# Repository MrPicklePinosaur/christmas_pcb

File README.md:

<div align="center">

# christmas pcb

</div>

Retrieving models from JLCPCB using the [JLC2KiCad](https://github.com/TousstNicolas/JLC2KiCad_lib) tool
```
JLC2KiCadLib C70378 -dir lib -model_dir models -footprint_lib footprints -symbol_lib_dir symbols
```

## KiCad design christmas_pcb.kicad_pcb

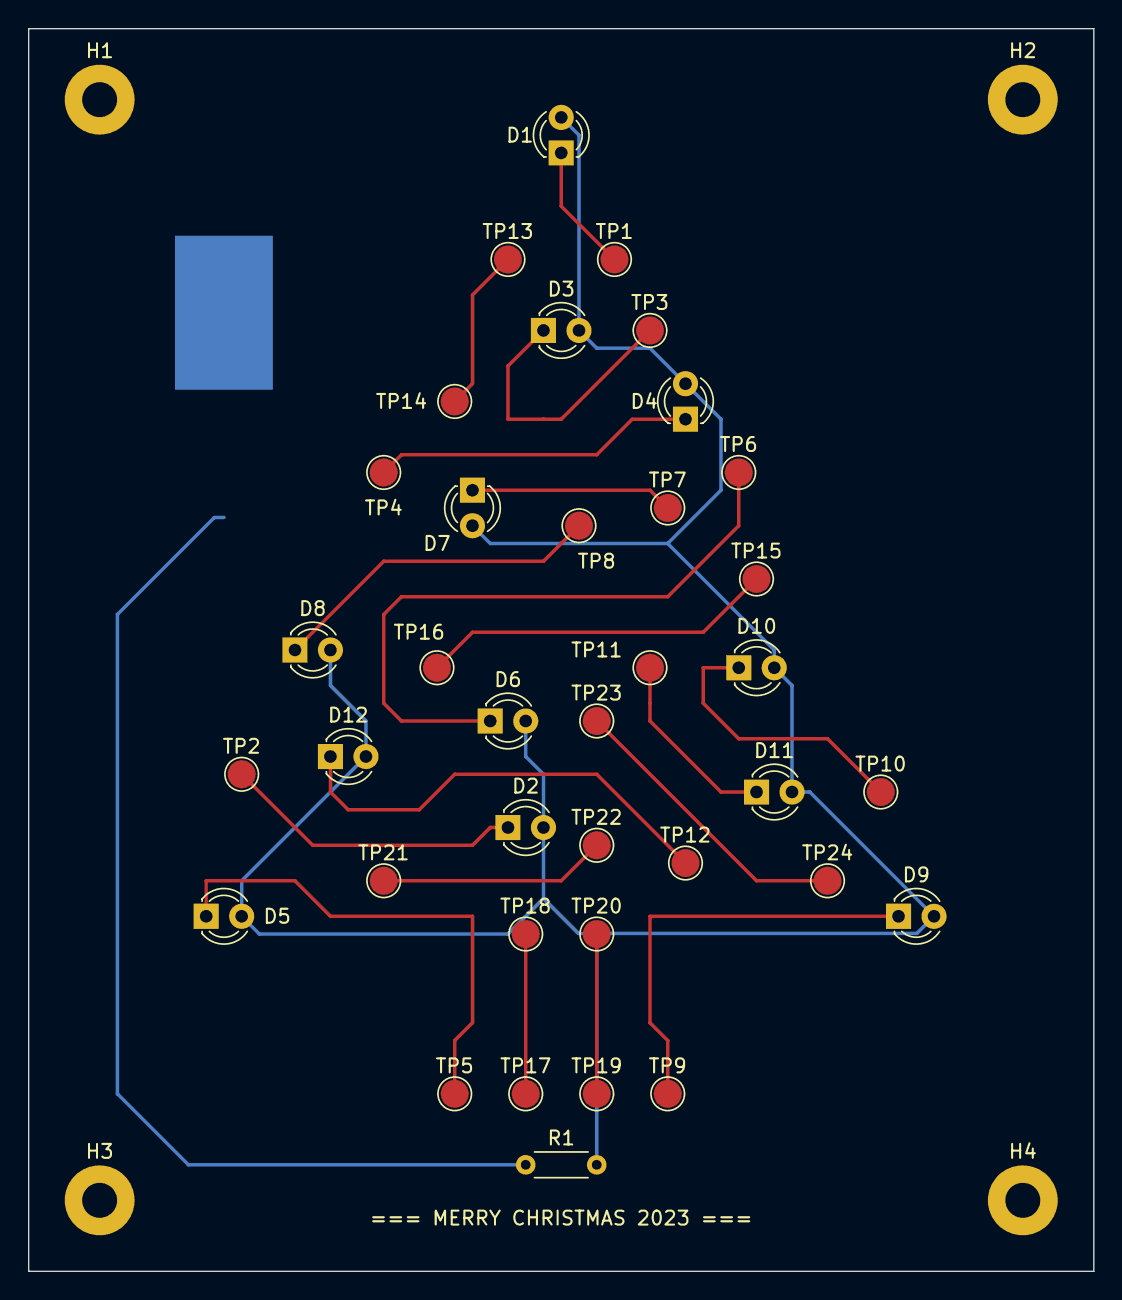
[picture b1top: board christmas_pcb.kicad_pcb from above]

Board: 2 copper layers, 76.2 x 88.9 mm, 42 parts (1 on the bottom side), 9 nets.

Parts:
BT1: Battery_Cell; BAT_BU2032SM-JJ-GTR
D1, D2, D3, D4, D5, D6, D7, D8, D9, D10, D11, D12: LED; LED_D3.0mm
H1, H2, H3, H4: MountingHole; MountingHole_2.5mm_Pad
R1: R; R_Axial_DIN0204_L3.6mm_D1.6mm_P5.08mm_Horizontal
TP1, TP2, TP3, TP4, TP5, TP6, TP7, TP8, TP9, TP10, TP11, TP12, TP13, TP14, TP15, TP16, TP17, TP18, TP19, TP20, TP21, TP22, TP23, TP24: TestPoint; TestPoint_Pad_D2.0mm

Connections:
GND: BT1.2 (-), D1.1 (K), D2.1 (K), D3.1 (K), D4.1 (K), D5.1 (K), D6.1 (K), D7.1 (K), D8.1 (K), D9.1 (K), D10.1 (K), D11.1 (K), D12.1 (K), TP1.1, TP2.1, TP3.1, TP4.1, TP5.1, TP6.1, TP7.1, TP8.1, TP9.1, TP10.1, TP11.1, TP12.1
unnamed: D1.2 (A), D2.2 (A), D3.2 (A), D4.2 (A), D5.2 (A), D6.2 (A), D7.2 (A), D8.2 (A), D9.2 (A), D10.2 (A), D11.2 (A), D12.2 (A), R1.2
unnamed: TP13.1, TP14.1
unnamed: TP15.1, TP18.1
unnamed: TP16.1, TP19.1
unnamed: TP17.1, TP20.1
unnamed: TP21.1, TP23.1
unnamed: TP22.1, TP24.1
VCC: BT1.1 (+), R1.1

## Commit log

2023-12-14 add files
2023-12-14 add footprint for battery
2023-12-14 fix errors and use SMT battery
2023-12-14 more fixes and footprints
